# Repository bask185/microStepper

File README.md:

# PCB files and source code for microsteppers

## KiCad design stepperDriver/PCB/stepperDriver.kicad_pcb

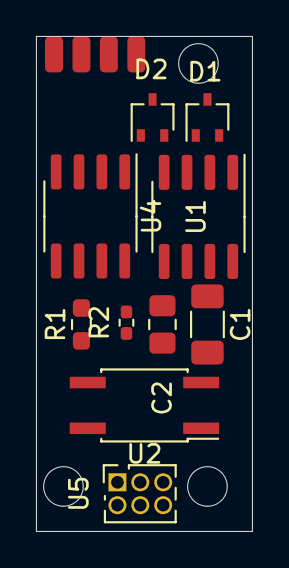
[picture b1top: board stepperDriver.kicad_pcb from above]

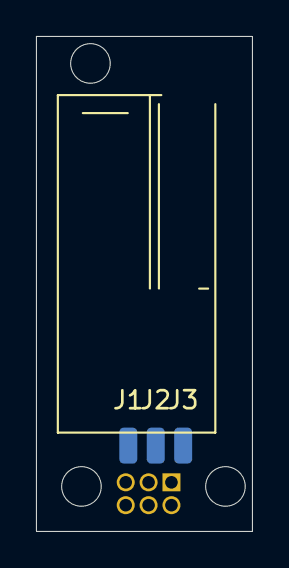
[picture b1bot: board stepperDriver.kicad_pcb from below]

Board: 2 copper layers, 12.0 x 27.5 mm, 17 parts (3 on the bottom side), 11 nets, no tracks yet.

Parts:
C1: CP; C_1206_3216Metric_Pad1.33x1.80mm_HandSolder
C2: C; C_0805_2012Metric_Pad1.18x1.45mm_HandSolder
D1, D2: BAT54CW; SOT-323_SC-70
J1, J2, J3: pin; SolderWirePad_1x01_SMD_1x2mm
J4, J5, J6, J7: mot; SolderWirePad_1x01_SMD_1x2mm
R1: 1k5; R_0603_1608Metric_Pad0.98x0.95mm_HandSolder
R2: R; R_0402_1005Metric_Pad0.72x0.64mm_HandSolder
U1: L78L05_SO8; SOIC-8_3.9x4.9mm_P1.27mm
U2: LTV-357T; SO-4_4.4x3.6mm_P2.54mm
U4: ATtiny13A-SS; SOIC-8_3.9x4.9mm_P1.27mm
U5: HEADER_3x2; PinSocket_2x03_P1.27mm_Vertical

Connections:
+5V: C2.1, D1.3, D2.3, R2.1, U1.1 (OUT), U4.8 (VCC), U5.5
/IN: U2.4, U4.7 (PB2), U5.4
/MISO: D2.1, J5.1, U4.6 (PB1), U5.6
/MOSI: D2.2, J4.1, U4.5 (PB0), U5.3
/RESET: R2.2, U4.1 (~RESET/PB5), U5.2
GND: C1.2, C2.2, J3.1, U1.2 (GND), U1.3 (GND), U1.6 (GND), U1.7 (GND), U2.3, U4.4 (GND), U5.1
unnamed: J2.1, U2.2
unnamed: R1.2, U2.1
unnamed: D1.2, J6.1, U4.2 (PB3)
unnamed: D1.1, J7.1, U4.3 (PB4)
VCC: C1.1, J1.1, R1.1, U1.8 (IN)

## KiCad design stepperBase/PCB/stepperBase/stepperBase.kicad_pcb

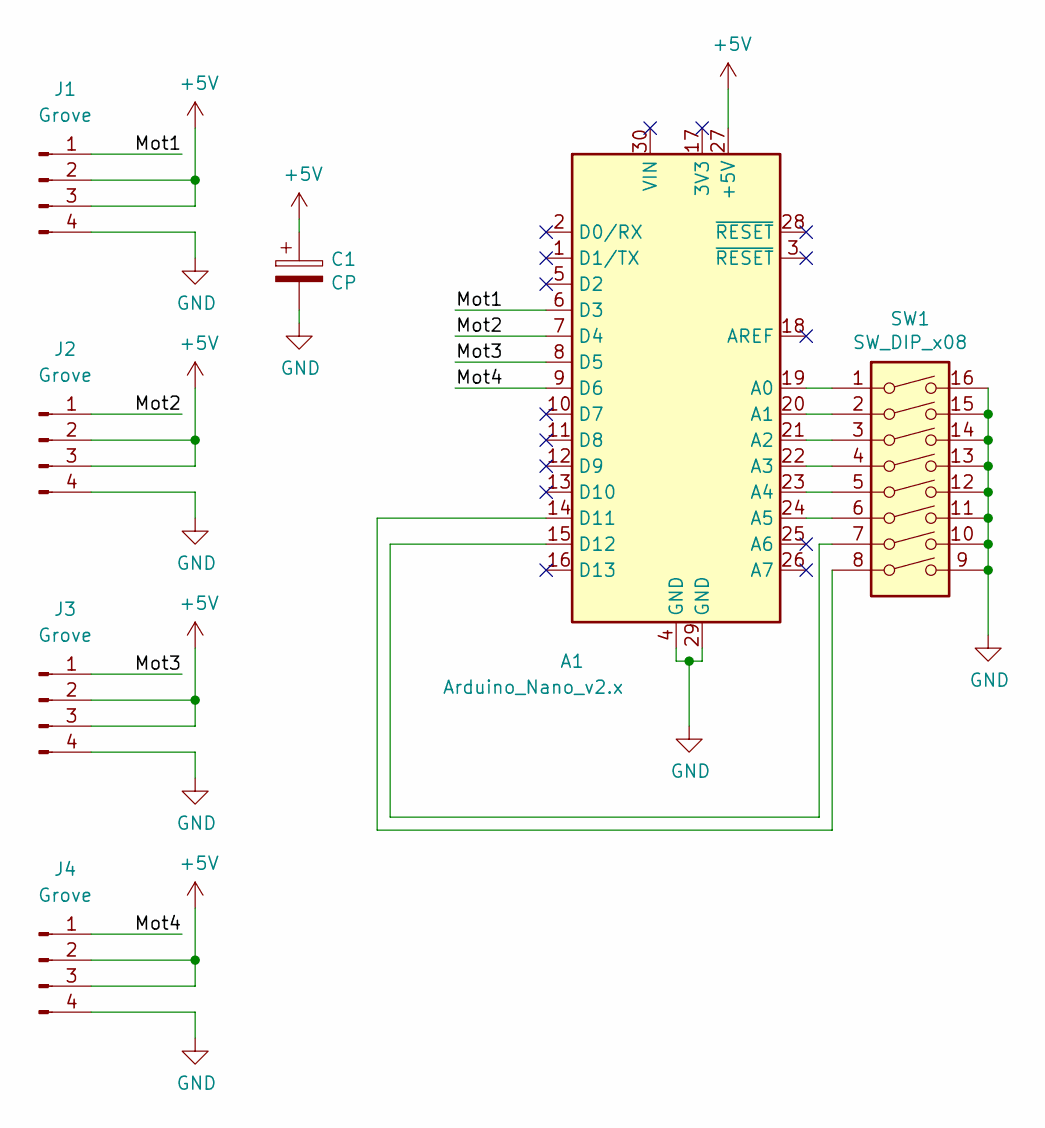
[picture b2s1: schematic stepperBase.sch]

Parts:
A1: Arduino_Nano_v2.x; Arduino_Nano
C1: CP; CP_Radial_D5.0mm_P2.50mm
J1, J2, J3, J4: Grove; NS-Tech_Grove_1x04_P2mm_Vertical
SW1: SW_DIP_x08; SW_DIP_SPSTx08_Slide_6.7x21.88mm_W7.62mm_P2.54mm_LowProfile

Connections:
+5V: A1.27 (+5V), C1.1, J1.2, J1.3, J2.2, J2.3, J3.2, J3.3, J4.2, J4.3
/Mot1: A1.6 (D3), J1.1
/Mot2: A1.7 (D4), J2.1
/Mot3: A1.8 (D5), J3.1
/Mot4: A1.9 (D6), J4.1
GND: A1.4 (GND), A1.29 (GND), C1.2, J1.4, J2.4, J3.4, J4.4, SW1.9, SW1.10, SW1.11, SW1.12, SW1.13, SW1.14, SW1.15, SW1.16
unnamed: A1.14 (D11), SW1.8
unnamed: A1.15 (D12), SW1.7
unnamed: A1.19 (A0), SW1.1
unnamed: A1.20 (A1), SW1.2
unnamed: A1.21 (A2), SW1.3
unnamed: A1.22 (A3), SW1.4
unnamed: A1.23 (A4), SW1.5
unnamed: A1.24 (A5), SW1.6

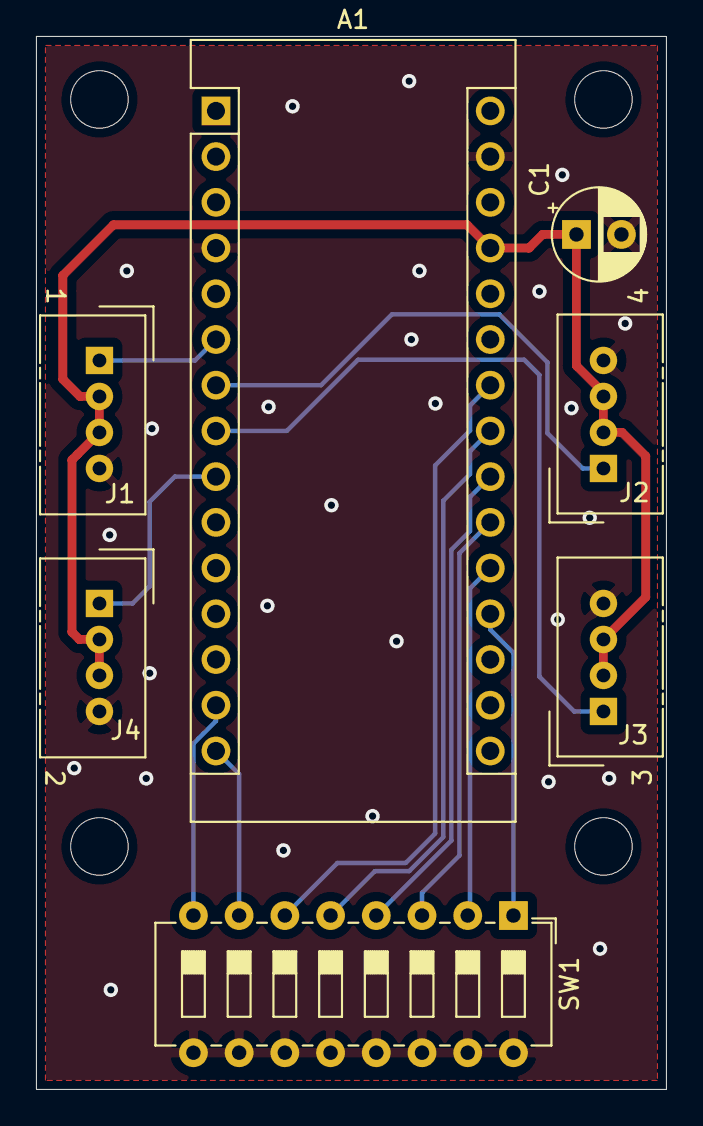
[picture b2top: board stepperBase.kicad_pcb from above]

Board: 2 copper layers, 35.0 x 58.5 mm, 7 parts (0 on the bottom side), 14 nets.

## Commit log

2023-03-07 changed schematic and made new PCB. I removed the DCC interface and rectifier
